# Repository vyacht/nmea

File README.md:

NMEA Wifi Router
====
Victor

Boards and modules for nmea wifi router. 

The files in this repository contain the schematics and boards of the 
vYacht Wifi Router. This router allows to connect directly to the NMEA 
network and distribute navigational information via Wifi or ethernet.

This router is certainly the easiest and most cost effective gateway between 
the NMEA boat on-board network and instruments and your PC or iPad/Android. All 
connections are fully isolated to avoid ground loops.

The router operates with the typical on-board 12V power supply. It has 
an efficient 12V to 3.3V step down buck converter. 

Software
====

The router runs a modified openwrt as operating system.

Availability
====

Fully assembled and professionally produced boards can be purchased via 
www.vyacht.net. 

License
====

If you are a private person you are free to use the design for any 
private use. 

NMEA Wifi Router and other designs by vyacht.net are licensed under a Creative Commons 
Attribution-NonCommercial-ShareAlike 3.0 Unported License.

The NMEA Wifi Router uses a RT3050 based Carambola as CPU and Wifi module. The Carambola 
board is unfortuntely based on a proprietary design and Ralink releases even data sheets 
only under NDA. But the Carambola board is currently the most cost effective and powerful 
Wifi and CPU solution known to me.

Version
====

Current version of this board is v8.

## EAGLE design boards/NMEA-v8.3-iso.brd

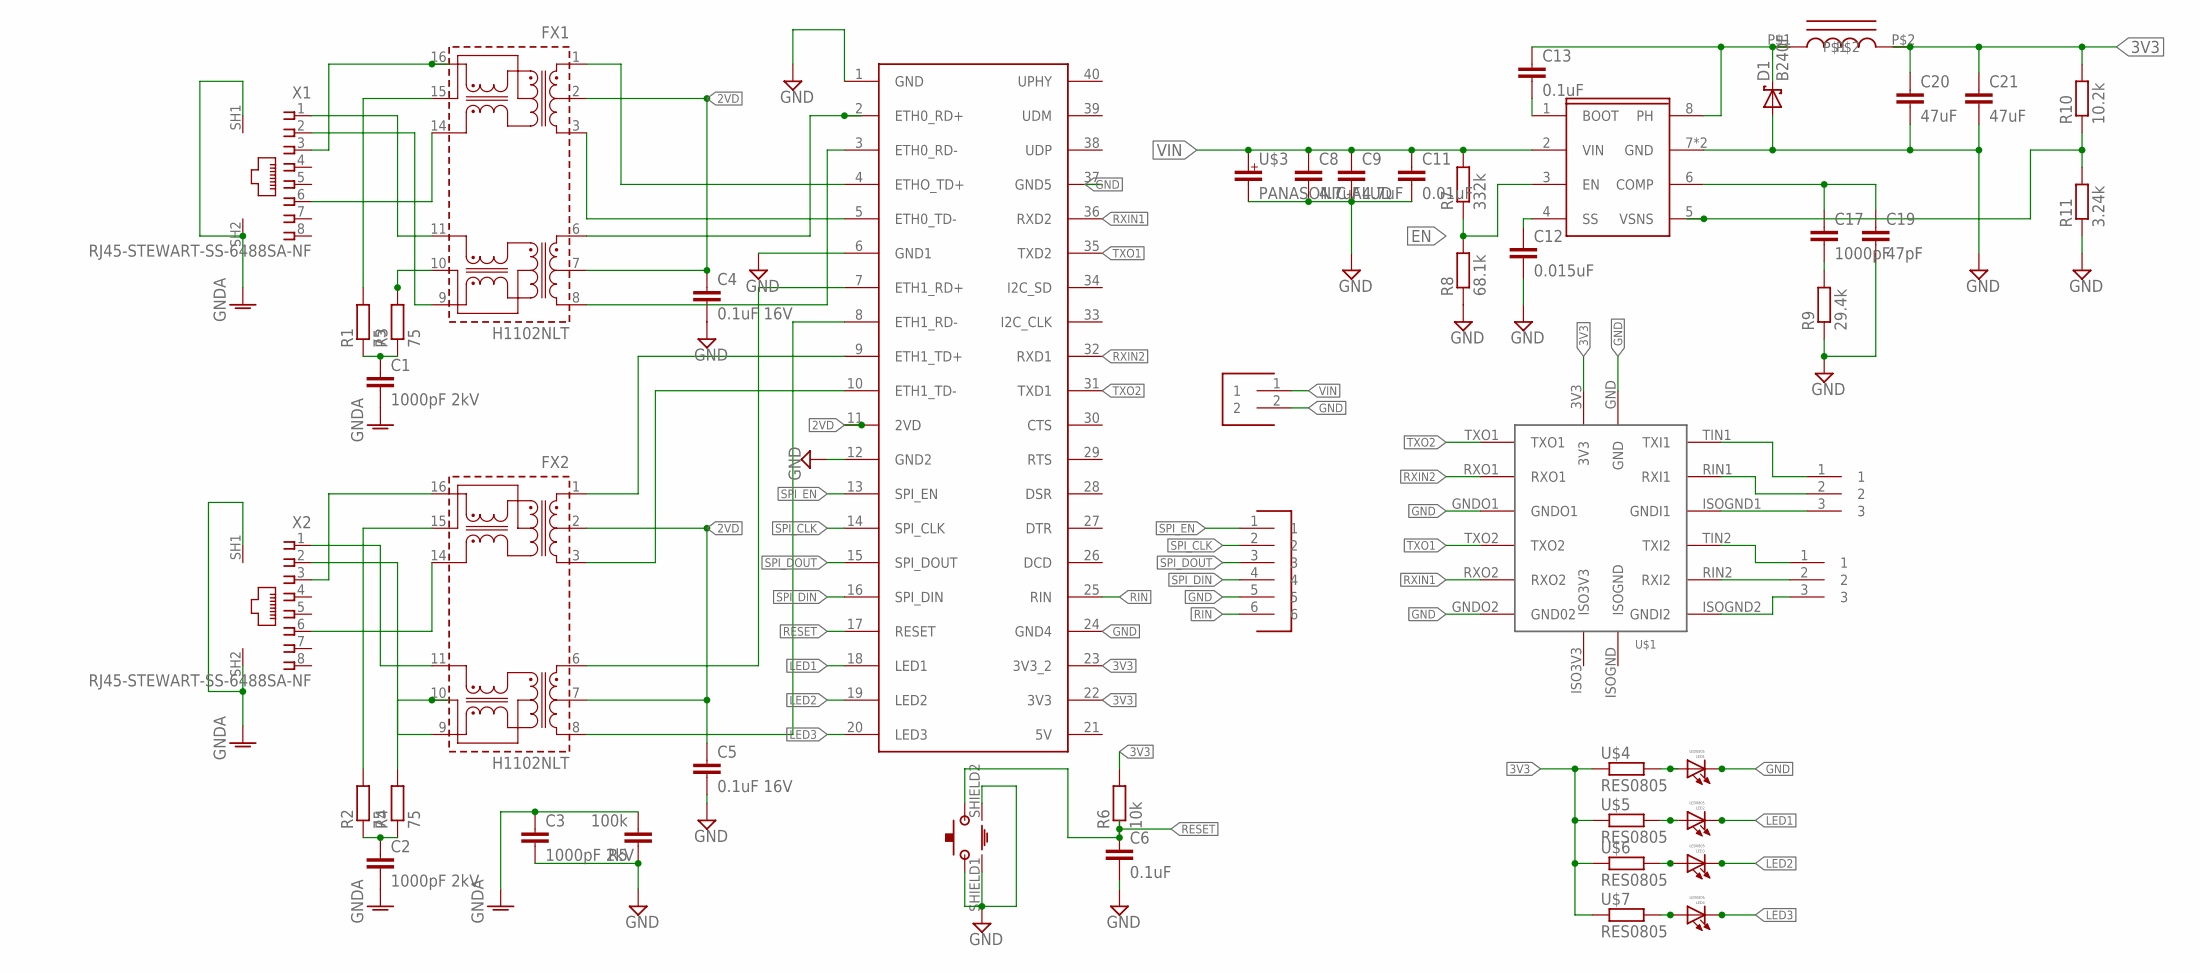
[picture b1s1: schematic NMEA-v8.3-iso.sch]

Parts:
C1, C2, C3: 1000pF 2kV; 1206
C4, C5: 0.1uF 16V; 0603
C6, C13: 0.1uF; 0603
C8, C9: 4.7uF; 1210
C11: 0.01uF; 0603
C12: 0.015uF; 0603
C17: 1000pF; 0603
C19: 47pF; 0603
C20, C21: 47uF; 1206
CARAMBOLA: CARAMBOLACREAM; CARAMBOLA-CREAM
D1: B240F; SMB
DATA1, DATA2: CON-3CREAM; CON-3-CREAM
FX1, FX2: H1102NLT; H/HX1XXXNL
J1: CON-5MM-2; CON--5MM-2
L1: CLF_TDK_INDUCTORCLF10040; CLF10040
LED1, LED2, LED3, LED4: LED0805; L0805
R1, R2, R3, R4: 75; 0603
R5: 100k; 1206
R6: 10k; 0603
R7: 332k; 0603
R8: 68.1k; 0603
R9: 29.4k; 0603
R10: 10.2k; 0603
R11: 3.24k; 0603
U8: TPS54231; SOIC-THERMAL
U$1: ISO-BOARDV1; ISO-BOARD
U$2: TACTILE-SWITCH-FSMRA1J
U$3: PANASONIC-ALUD; PANASONIC_D
U$4, U$5, U$6, U$7: RES0805; 0603
U$8: CON-6
X1, X2: RJ45-STEWART-SS-6488SA-NF; RJ45-STEWART-6488

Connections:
2VD: C4.1, C5.1, CARAMBOLA.11 (2VD), FX1.2, FX1.7, FX2.2, FX2.7
3V3: C20.1, C21.1, CARAMBOLA.22 (3V3), CARAMBOLA.23 (3V3_2), L1.P$2, R6.2, R10.2, U$1.3V3, U$4.1, U$5.1, U$6.1, U$7.1
EN: R7.1, R8.2, U8.3 (EN)
ETH1_RD-: CARAMBOLA.8 (ETH1_RD-), FX2.8
GND: C3.2, C4.2, C5.2, C6.2, C8.2, C9.2, C11.2, C12.2, C19.2, C20.2, C21.2, CARAMBOLA.1 (GND), CARAMBOLA.6 (GND1), CARAMBOLA.12 (GND2), CARAMBOLA.24 (GND4), CARAMBOLA.37 (GND5), D1.A, J1.2, LED1.C, R5.1, R8.1, R9.1, R11.1, U8.7 (GND), U8.P$1 (GND), U$1.GND, U$1.GNDO1, U$1.GNDO2 (GND02), U$2.2, U$2.SHIELD1, U$2.SHIELD2, U$3.-, U$8.5
GNDA: C1.2, C2.2, C3.1, R5.2, X1.SH1, X1.SH2, X2.SH1, X2.SH2
ISOGND1: DATA1.3, U$1.ISOGND1 (GNDI1)
ISOGND2: DATA2.3, U$1.ISOGND2 (GNDI2)
LED1: CARAMBOLA.18 (LED1), LED2.C
LED2: CARAMBOLA.19 (LED2), LED3.C
LED3: CARAMBOLA.20 (LED3), LED4.C
unnamed: CARAMBOLA.4 (ETHO_TD+), FX1.1
unnamed: C13.2, U8.1 (BOOT)
unnamed: LED1.A, U$4.2
unnamed: LED2.A, U$5.2
unnamed: LED3.A, U$6.2
unnamed: R10.1, R11.2, U8.5 (VSNS)
unnamed: C17.1, C19.1, U8.6 (COMP)
unnamed: C17.2, R9.2
unnamed: LED4.A, U$7.2
unnamed: CARAMBOLA.2 (ETH0_RD+), FX1.6
unnamed: CARAMBOLA.5 (ETH0_TD-), FX1.3
unnamed: CARAMBOLA.3 (ETH0_RD-), FX1.8
unnamed: C2.1, R2.1, R4.1
unnamed: FX1.10, R3.2
unnamed: FX1.15, R1.2
unnamed: C1.1, R1.1, R3.1
unnamed: FX1.11, X1.1
unnamed: FX1.9, X1.2
unnamed: FX1.16, X1.3
unnamed: FX1.14, X1.6
unnamed: CARAMBOLA.7 (ETH1_RD+), FX2.6
unnamed: CARAMBOLA.9 (ETH1_TD+), FX2.1
unnamed: CARAMBOLA.10 (ETH1_TD-), FX2.3
unnamed: FX2.15, R2.2
unnamed: FX2.10, R4.2
unnamed: FX2.16, X2.3
unnamed: FX2.11, X2.1
unnamed: FX2.14, X2.6
unnamed: FX2.9, X2.2
PH: C13.1, D1.C, L1.P$1, U8.8 (PH)
RESET: C6.1, CARAMBOLA.17 (RESET), R6.1, U$2.1
RIN: CARAMBOLA.25 (RIN), U$8.6
RIN1: DATA1.2, U$1.RIN1 (RXI1)
RIN2: DATA2.2, U$1.RIN2 (RXI2)
RXIN1: CARAMBOLA.36 (RXD2), U$1.RXO2
RXIN2: CARAMBOLA.32 (RXD1), U$1.RXO1
SPI_CLK: CARAMBOLA.14 (SPI_CLK), U$8.2
SPI_DIN: CARAMBOLA.16 (SPI_DIN), U$8.4
SPI_DOUT: CARAMBOLA.15 (SPI_DOUT), U$8.3
SPI_EN: CARAMBOLA.13 (SPI_EN), U$8.1
SS: C12.1, U8.4 (SS)
TIN1: DATA1.1, U$1.TIN1 (TXI1)
TIN2: DATA2.1, U$1.TIN2 (TXI2)
TXO1: CARAMBOLA.35 (TXD2), U$1.TXO2
TXO2: CARAMBOLA.31 (TXD1), U$1.TXO1
VIN: C8.1, C9.1, C11.1, J1.1, R7.2, U8.2 (VIN), U$3.+

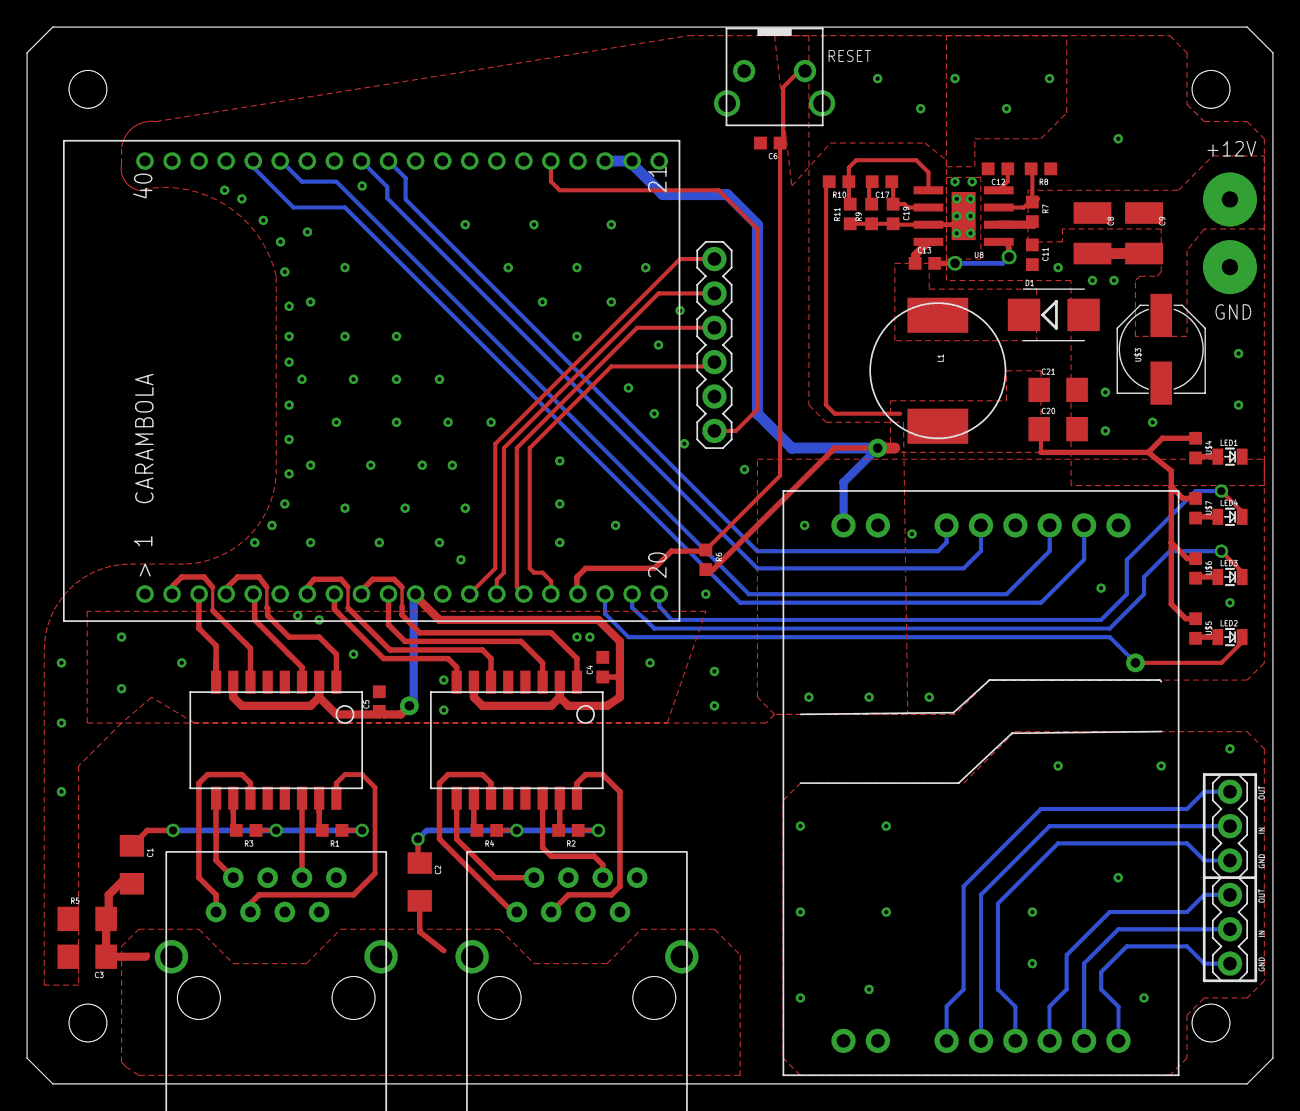
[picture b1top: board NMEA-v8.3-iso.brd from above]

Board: 2 copper layers, 92.1 x 78.1 mm, 49 parts (0 on the bottom side), 57 nets.

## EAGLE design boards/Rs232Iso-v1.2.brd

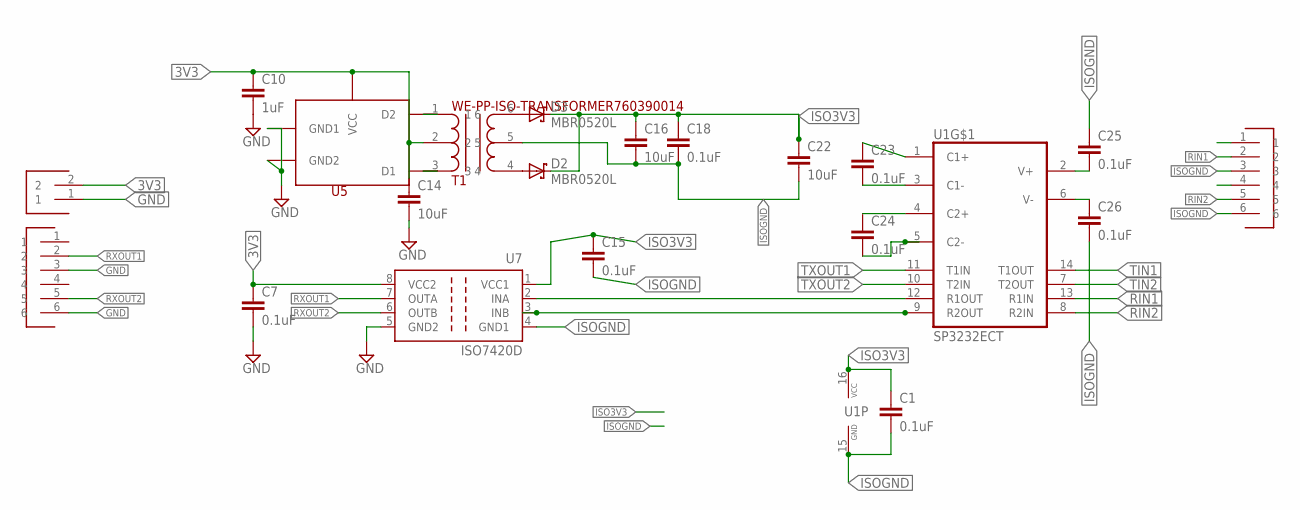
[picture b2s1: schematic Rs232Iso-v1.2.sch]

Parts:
C1, C7, C15, C18, C23, C24, C25, C26: 0.1uF; 0603
C10: 1uF; 0805
C14, C16, C22: 10uF; 0805
D2, D3: MBR0520L; SOD123
J1: CON-2STD-2.54; CON-2
J2, J4: CON-6
T1: WE-PP-ISO-TRANSFORMER760390014; WE_TRANSFORMER
U1: SP3232ECT; SO16
U5: SN6501DBVT; SOT23-5L
U7: ISO7420D; SO08

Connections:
3V3: C7.1, C10.1, C14.1, J1.2, T1.2, U5.2 (VCC), U7.8 (VCC2)
GND: C7.2, C10.2, C14.2, J1.1, J4.3, J4.6, U5.4 (GND1), U5.5 (GND2), U7.5 (GND2)
ISO3V3: C1.1, C15.1, C16.1, C18.1, C22.1, D2.C, D3.C, U1.16 (VCC), U7.1 (VCC1)
ISOGND: C1.2, C15.2, C16.2, C18.2, C22.2, C25.1, C26.2, J2.3, J2.6, T1.5, U1.15 (GND), U7.4 (GND1)
unnamed: D3.A, T1.6
unnamed: D2.A, T1.4
unnamed: T1.1, U5.3 (D2)
unnamed: T1.3, U5.1 (D1)
unnamed: C23.2, U1.3 (C1-)
unnamed: U1.12 (R1OUT), U7.2 (INA)
unnamed: C24.1, U1.4 (C2+)
unnamed: U1.9 (R2OUT), U7.3 (INB)
unnamed: C24.2, U1.5 (C2-)
unnamed: C23.1, U1.1 (C1+)
RIN1: J2.2, U1.13 (R1IN)
RIN2: J2.5, U1.8 (R2IN)
RXOUT1: J4.2, U7.7 (OUTA)
RXOUT2: J4.5, U7.6 (OUTB)
TIN1: U1.14 (T1OUT)
TIN2: U1.7 (T2OUT)
TXOUT1: U1.11 (T1IN)
TXOUT2: U1.10 (T2IN)
V+: C25.2, U1.2 (V+)
V-: C26.1, U1.6 (V-)

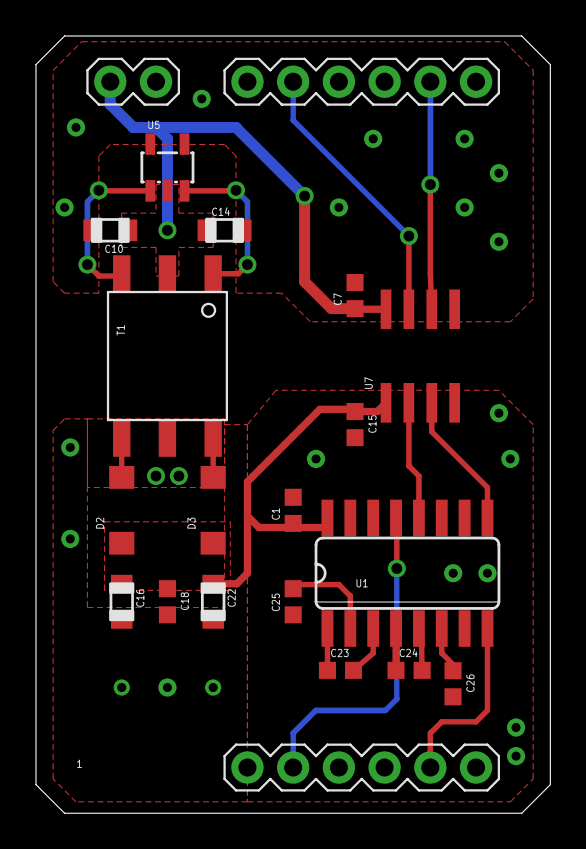
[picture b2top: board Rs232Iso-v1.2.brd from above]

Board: 2 copper layers, 28.6 x 43.2 mm, 21 parts (0 on the bottom side), 20 nets.

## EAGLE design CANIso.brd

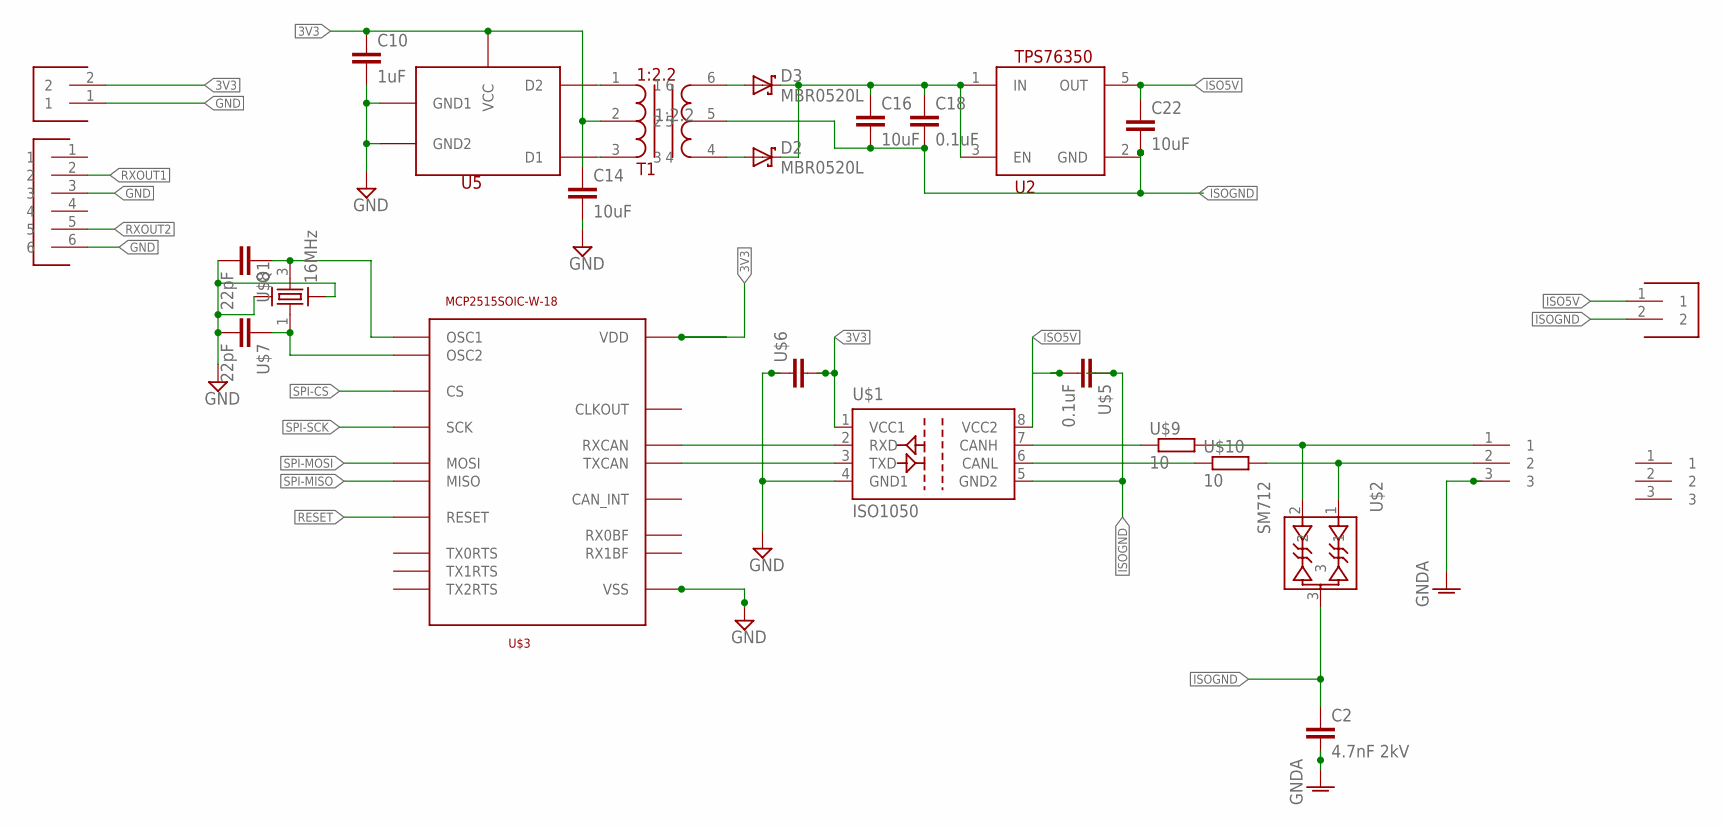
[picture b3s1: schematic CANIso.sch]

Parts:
C2: 4.7nF 2kV; 0805
C10: 1uF; 0805
C14, C16, C22: 10uF; 0805
C18: 0.1uF; 0805
D2, D3: MBR0520L; SOD123
J1, J3: CON-2STD-2.54; CON-2
J4: CON-6
Q1: 16MHz; ABM3B
T1: 1:2.2; WE_TRANSFORMER
U2: TPS76350; SOT23-5L
U5: SN6501DBVT; SOT23-5L
U$1: ISO1050; DUB
U$2: SM712; SOT23-3L
U$3: MCP2515SOIC-W-18; SOIC-W-18
U$4, U$11: CON-3
U$5: 0.1uF; 0805
U$6: CAP0805; 0805
U$7, U$8: 22pF; 0805
U$9, U$10: 10; 0805

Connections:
3V3: C10.1, C14.1, J1.2, T1.2, U5.2 (VCC), U$1.1 (VCC1), U$3.18 (VDD), U$6.2
GND: C10.2, C14.2, J1.1, J4.3, J4.6, Q1.2 (GND), Q1.4 (GND2), U5.4 (GND1), U5.5 (GND2), U$1.4 (GND1), U$3.9 (VSS), U$6.1, U$7.2, U$8.2
GNDA: C2.2, U$4.3
ISO5V: C22.1, J3.1, U2.5 (OUT), U$1.8 (VCC2)
ISOGND: C2.1, C16.2, C18.2, C22.2, J3.2, T1.5, U2.2 (GND), U$1.5 (GND2), U$2.3, U$5.1
LDOIN: C16.1, C18.1, D2.C, D3.C, U2.1 (IN), U2.3 (EN)
unnamed: D3.A, T1.6
unnamed: D2.A, T1.4
unnamed: U$1.7 (CANH), U$9.1
unnamed: T1.1, U5.3 (D2)
unnamed: T1.3, U5.1 (D1)
unnamed: U$1.2 (RXD), U$3.2 (RXCAN)
unnamed: U$1.3 (TXD), U$3.1 (TXCAN)
unnamed: U$2.2, U$4.1, U$9.2
unnamed: Q1.3 (2), U$3.8 (OSC1), U$8.1
unnamed: Q1.1, U$3.7 (OSC2), U$7.1
unnamed: U$2.1, U$4.2, U$10.2
unnamed: U$1.6 (CANL), U$10.1
RESET: U$3.17 (RESET)
RXOUT1: J4.2
RXOUT2: J4.5
SPI-CS: U$3.16 (CS)
SPI-MISO: U$3.15 (MISO)
SPI-MOSI: U$3.14 (MOSI)
SPI-SCK: U$3.13 (SCK)

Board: 2 copper layers, 26 parts (0 on the bottom side), 18 nets, no tracks yet.

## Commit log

2013-04-14 Bord version 8
2013-04-14 readme update
2013-04-14 adding CAN/RS232
2013-04-14 rename
2013-04-14 remove old files
2013-04-24 adding iomode startup scripts
2013-08-27 update working tree from custom feed
2013-08-27 adding latest boards
2013-08-27 adding case files
2013-08-27 removing board files from main dir, keeping newer in boards-dir
2016-11-08 Изменение Виктор
